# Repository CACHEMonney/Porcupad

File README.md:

# Porcupad
A Hackpad project you probably shouldn't touch

Life is convient and everyone is constantly looking for ways to make it even easier it's too good too free too nice... it need to stop.

so i made a macropad that makes your life harder :) divided int 3 layers each gets increasingly more annoying until the last layer which i recommend you never use someone once told me the keyboard is the most trusted device on the computer so i thought of how that trust can be abused

thinking

schematic

pcb

frame

XIAO RP2040 (1) *https://www.aliexpress.com/item/1005004459618789.html?spm=a2g0o.cart.0.0.622638daGxySK1&mp=1&pdp_npi=5%40dis%21GBP%21GBP%205.45%21GBP%204.09%21%21GBP%204.09%21%21%21%40211b61d017539458504471040e2837%2112000039319962127%21ct%21UK%216396990757%21%211%210&pdp_ext_f=%7B%22cart2PdpParams%22%3A%7B%22pdpBusinessMode%22%3A%22retail%22%7D%7D

MX-Style switches (8) *https://www.aliexpress.com/item/1005005426750916.html?spm=a2g0o.cart.0.0.622638daGxySK1&mp=1&pdp_npi=5%40dis%21GBP%21GBP%201.79%21GBP%201.25%21%21GBP%201.25%21%21%21%40211b61d017539458504471040e2837%2112000033021986678%21ct%21UK%216396990757%21%211%210

M3x16mm screws (4) *https://www.aliexpress.com/item/1005007346978106.html?spm=a2g0o.cart.0.0.622638daGxySK1&mp=1&pdp_npi=5%40dis%21GBP%21GBP%202.22%21GBP%202.22%21%21GBP%202.22%21%21%21%40211b61d017539458504471040e2837%2112000040360249873%21ct%21UK%216396990757%21%211%210

EC11 rotarary encoder (1) *https://www.aliexpress.com/item/1005005983134515.html?spm=a2g0o.cart.0.0.622638daGxySK1&mp=1&pdp_npi=5%40dis%21GBP%21GBP%201.10%21GBP%201.10%21%21GBP%201.10%21%21%21%40211b61d017539458504471040e2837%2112000035172713582%21ct%21UK%216396990757%21%211%210&pdp_ext_f=%7B%22cart2PdpParams%22%3A%7B%22pdpBusinessMode%22%3A%22retail%22%7D%7D

THROUGH HOLE 1N4148 diode (8) *https://www.aliexpress.com/item/4000142272546.html?spm=a2g0o.cart.0.0.622638daGxySK1&mp=1&pdp_npi=5%40dis%21GBP%21GBP%201.34%21GBP%200.77%21%21GBP%200.77%21%21%21%40211b61d017539458504471040e2837%2110000000428321629%21ct%21UK%216396990757%21%211%210&pdp_ext_f=%7B%22cart2PdpParams%22%3A%7B%22pdpBusinessMode%22%3A%22retail%22%7D%7D

Subtotal $18.81

PCB *https://jlcpcb.com/

Subtotal $28.20

Case print (top and bottom) *done by my friend

Total $47.01

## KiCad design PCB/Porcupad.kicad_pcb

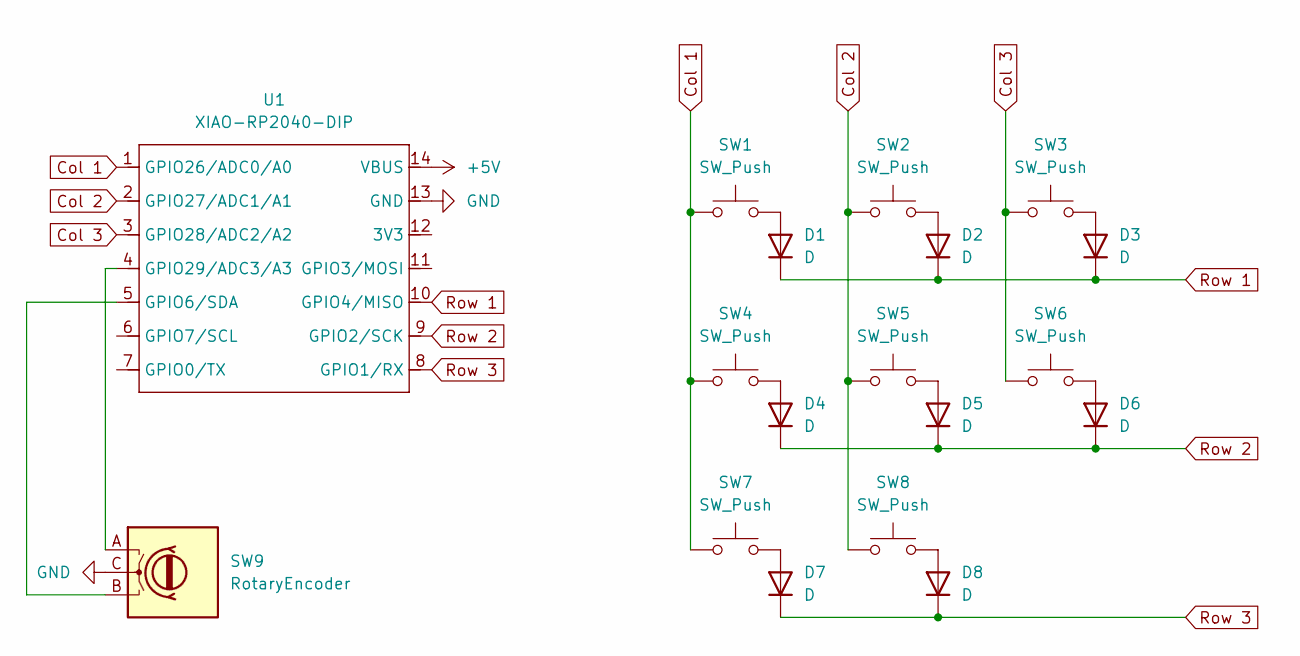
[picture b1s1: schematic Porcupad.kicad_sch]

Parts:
D1, D2, D3, D4, D5, D6, D7, D8: D; D_DO-35_SOD27_P7.62mm_Horizontal
SW1, SW2, SW3, SW4, SW5, SW6, SW7, SW8: SW_Push; SW_Cherry_MX_1.00u_PCB
SW9: RotaryEncoder; RotaryEncoder_Alps_EC11E-Switch_Vertical_H20mm
U1: XIAO-RP2040-DIP

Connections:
+5V: U1.14 (VBUS)
Col 1: SW1.1, SW4.1, SW7.1, U1.1 (GPIO26/ADC0/A0)
Col 2: SW2.1, SW5.1, SW8.1, U1.2 (GPIO27/ADC1/A1)
Col 3: SW3.1, SW6.1, U1.3 (GPIO28/ADC2/A2)
GND: SW9.C, U1.13 (GND)
unnamed: D1.2 (A), SW1.2
unnamed: D2.2 (A), SW2.2
unnamed: D3.2 (A), SW3.2
unnamed: D4.2 (A), SW4.2
unnamed: D5.2 (A), SW5.2
unnamed: D6.2 (A), SW6.2
unnamed: D7.2 (A), SW7.2
unnamed: D8.2 (A), SW8.2
unnamed: SW9.B, U1.5 (GPIO6/SDA)
unnamed: SW9.A, U1.4 (GPIO29/ADC3/A3)
Row 1: D1.1 (K), D2.1 (K), D3.1 (K), U1.10 (GPIO4/MISO)
Row 2: D4.1 (K), D5.1 (K), D6.1 (K), U1.9 (GPIO2/SCK)
Row 3: D7.1 (K), D8.1 (K), U1.8 (GPIO1/RX)

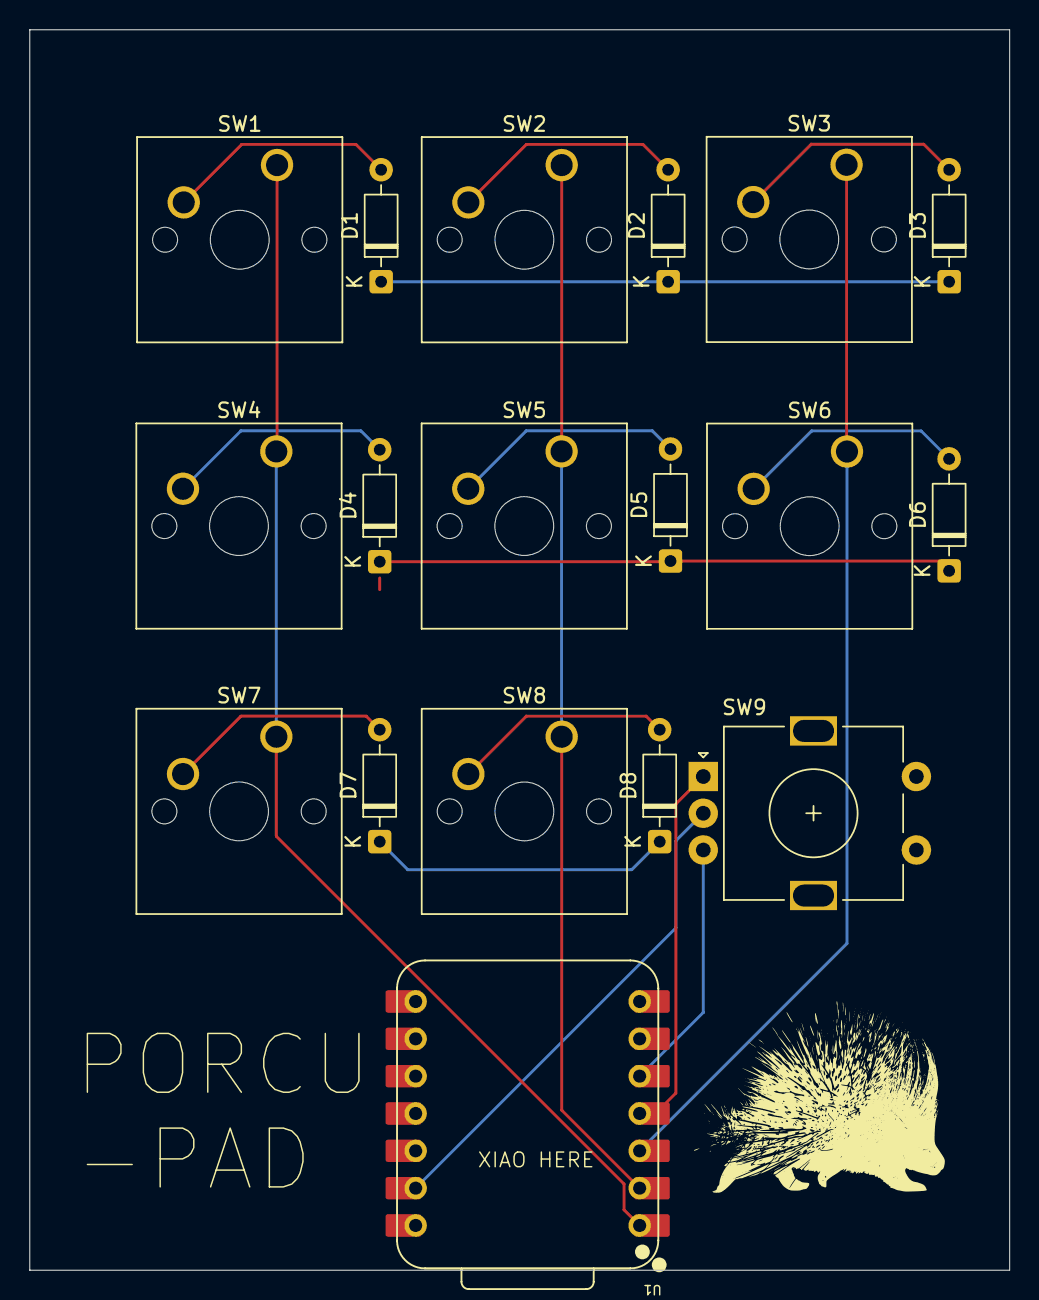
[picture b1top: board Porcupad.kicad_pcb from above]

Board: 2 copper layers, 66.7 x 84.4 mm, 18 parts (0 on the bottom side), 17 nets.

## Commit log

2025-07-31 Add files via upload
    PCB
